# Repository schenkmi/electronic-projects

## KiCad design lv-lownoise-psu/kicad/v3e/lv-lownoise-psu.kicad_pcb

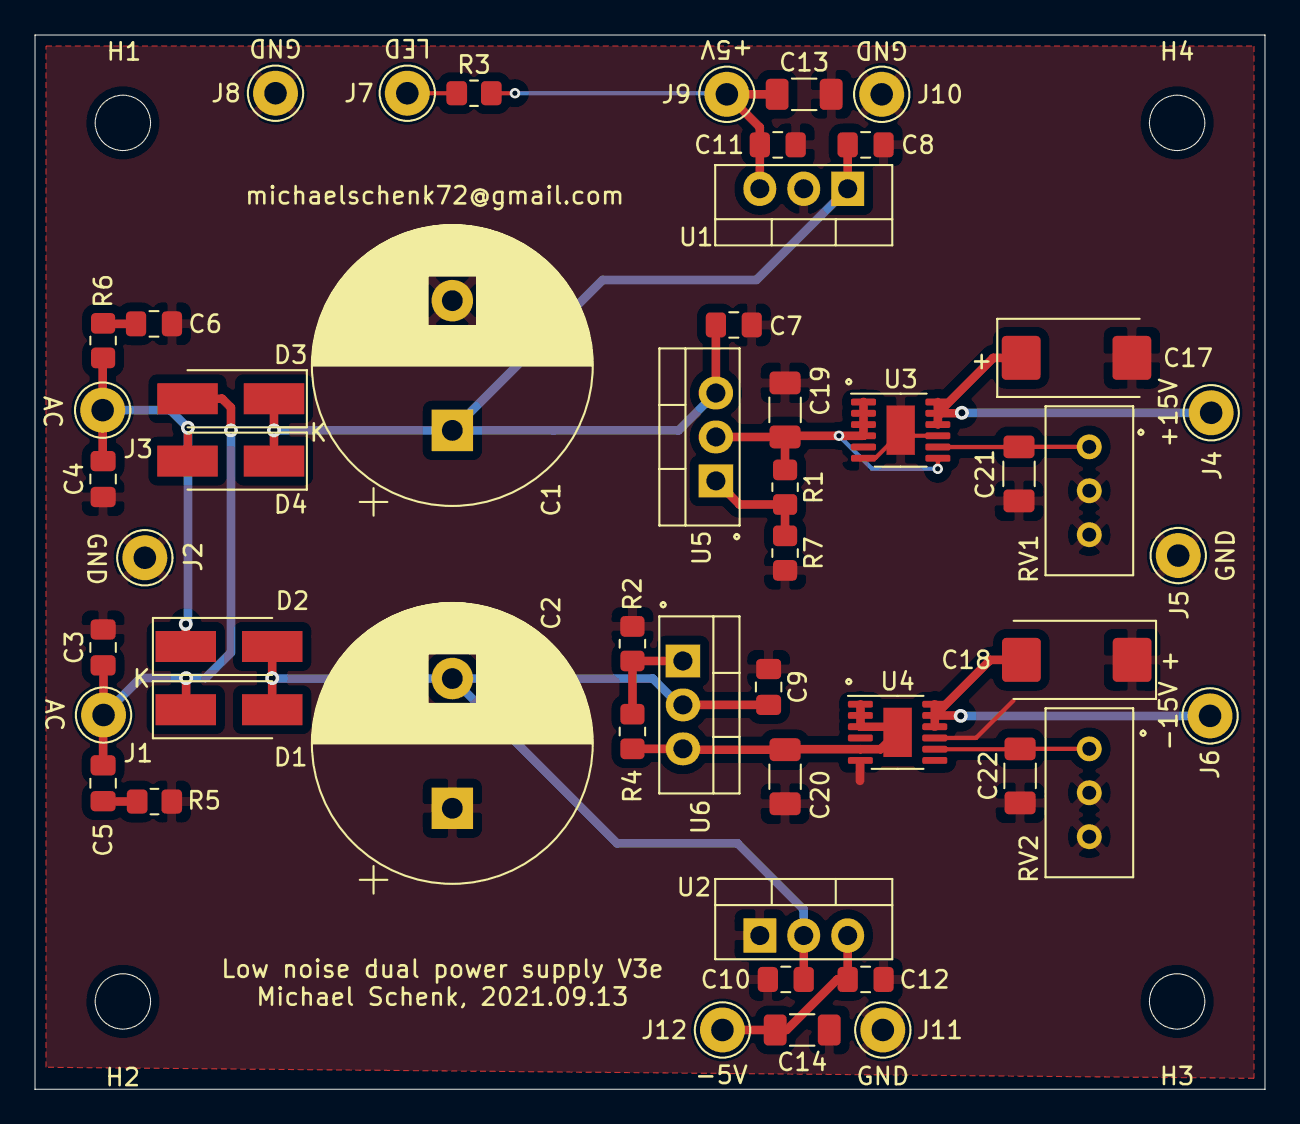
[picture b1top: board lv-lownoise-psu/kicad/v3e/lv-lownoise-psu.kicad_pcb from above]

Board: 2 copper layers, 71.1 x 61.0 mm, 55 parts (0 on the bottom side), 18 nets.

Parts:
C1, C2: 2200uF; CP_Radial_D16.0mm_P7.50mm
C3, C4: Cx/10nF/50V; C_0805_2012Metric_Pad1.18x1.45mm_HandSolder
C5, C6: Cs/50V; C_0805_2012Metric_Pad1.18x1.45mm_HandSolder
C7, C8, C9, C10: 330nF; C_0805_2012Metric_Pad1.18x1.45mm_HandSolder
C11, C12: 100nF; C_0805_2012Metric_Pad1.18x1.45mm_HandSolder
C13, C14: 10uF/25V; C_1206_3216Metric_Pad1.33x1.80mm_HandSolder
C17, C18: 33uF; CP_EIA-7343-31_Kemet-D_Pad2.25x2.55mm_HandSolder
C19, C20, C21, C22: 4.7uF/25V; C_1206_3216Metric_Pad1.33x1.80mm_HandSolder
D1, D2, D3, D4: BYG20D; D_SMA_Handsoldering
H1, H2, H3, H4: MountingHole; MountingHole_3.2mm_M3
J1, J3: AC; Pin_D1.3mm_L11.0mm
J2, J5, J8, J10, J11: GND; Pin_D1.3mm_L11.0mm
J4: +15V; Pin_D1.3mm_L11.0mm
J6: -15V; Pin_D1.3mm_L11.0mm
J7: LED; Pin_D1.3mm_L11.0mm
J9: +5V; Pin_D1.3mm_L11.0mm
J12: -5V; Pin_D1.3mm_L11.0mm
R1, R4: 270R; R_0805_2012Metric_Pad1.20x1.40mm_HandSolder
R2, R7: 3k3; R_0805_2012Metric_Pad1.20x1.40mm_HandSolder
R3: 240R; R_0805_2012Metric_Pad1.20x1.40mm_HandSolder
R5, R6: Rs/1/8W; R_0805_2012Metric_Pad1.20x1.40mm_HandSolder
RV1, RV2: 200k; Potentiometer_Bourns_3296W_Vertical
U1: LM7805_TO220; TO-220-3_Vertical
U2: LM7905_TO220; TO-220-3_Vertical
U3: LT3045xMSE; MSOP-12-1EP_3x4mm_P0.65mm_EP1.65x2.85mm
U4: LT3094xMSE; MSOP-12-1EP_3x4mm_P0.65mm_EP1.65x2.85mm
U5: LM317_TO-220; TO-220-3_Vertical
U6: LM337_TO220; TO-220-3_Vertical

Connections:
GND: C1.2, C2.1, C3.2, C4.1, C6.1, C7.2, C8.2, C9.1, C10.1, C11.2, C12.1, C13.2, C14.1, C17.2, C18.1, C19.2, C20.1, C21.2, C22.1, J2.1, J5.1, J8.1, J10.1, J11.1, R2.1, R5.2, R7.2, RV1.2, RV1.3, RV2.2, RV2.3, U1.2, U2.1, U3.6, U3.9, U3.13, U4.6, U4.9
unnamed: C1.1, C7.1, C8.1, D3.1, D4.1, U1.1, U5.3
unnamed: C3.1, C5.1, D1.1, D3.2, J1.1
unnamed: C4.2, D2.1, D4.2, J3.1, R6.2
unnamed: C5.2, R5.1
unnamed: C6.2, R6.1
unnamed: C2.2, C9.2, C10.2, D1.2, D2.2, U2.2, U6.2
unnamed: C11.1, C13.1, J9.1, R3.2, U1.3
unnamed: C12.2, C14.2, J12.1, U2.3
unnamed: C17.1, J4.1, U3.10, U3.11, U3.12
unnamed: C18.2, J6.1, U4.10, U4.11, U4.12
unnamed: C19.1, R1.1, U3.1, U3.2, U3.3, U3.4, U3.7, U5.2
unnamed: C20.2, R4.2, U4.1, U4.2, U4.3, U4.5, U4.13, U6.3
unnamed: C21.1, RV1.1, U3.8
unnamed: C22.2, RV2.1, U4.8
unnamed: J7.1, R3.1
unnamed: R1.2, R7.1, U5.1
unnamed: R2.2, R4.1, U6.1

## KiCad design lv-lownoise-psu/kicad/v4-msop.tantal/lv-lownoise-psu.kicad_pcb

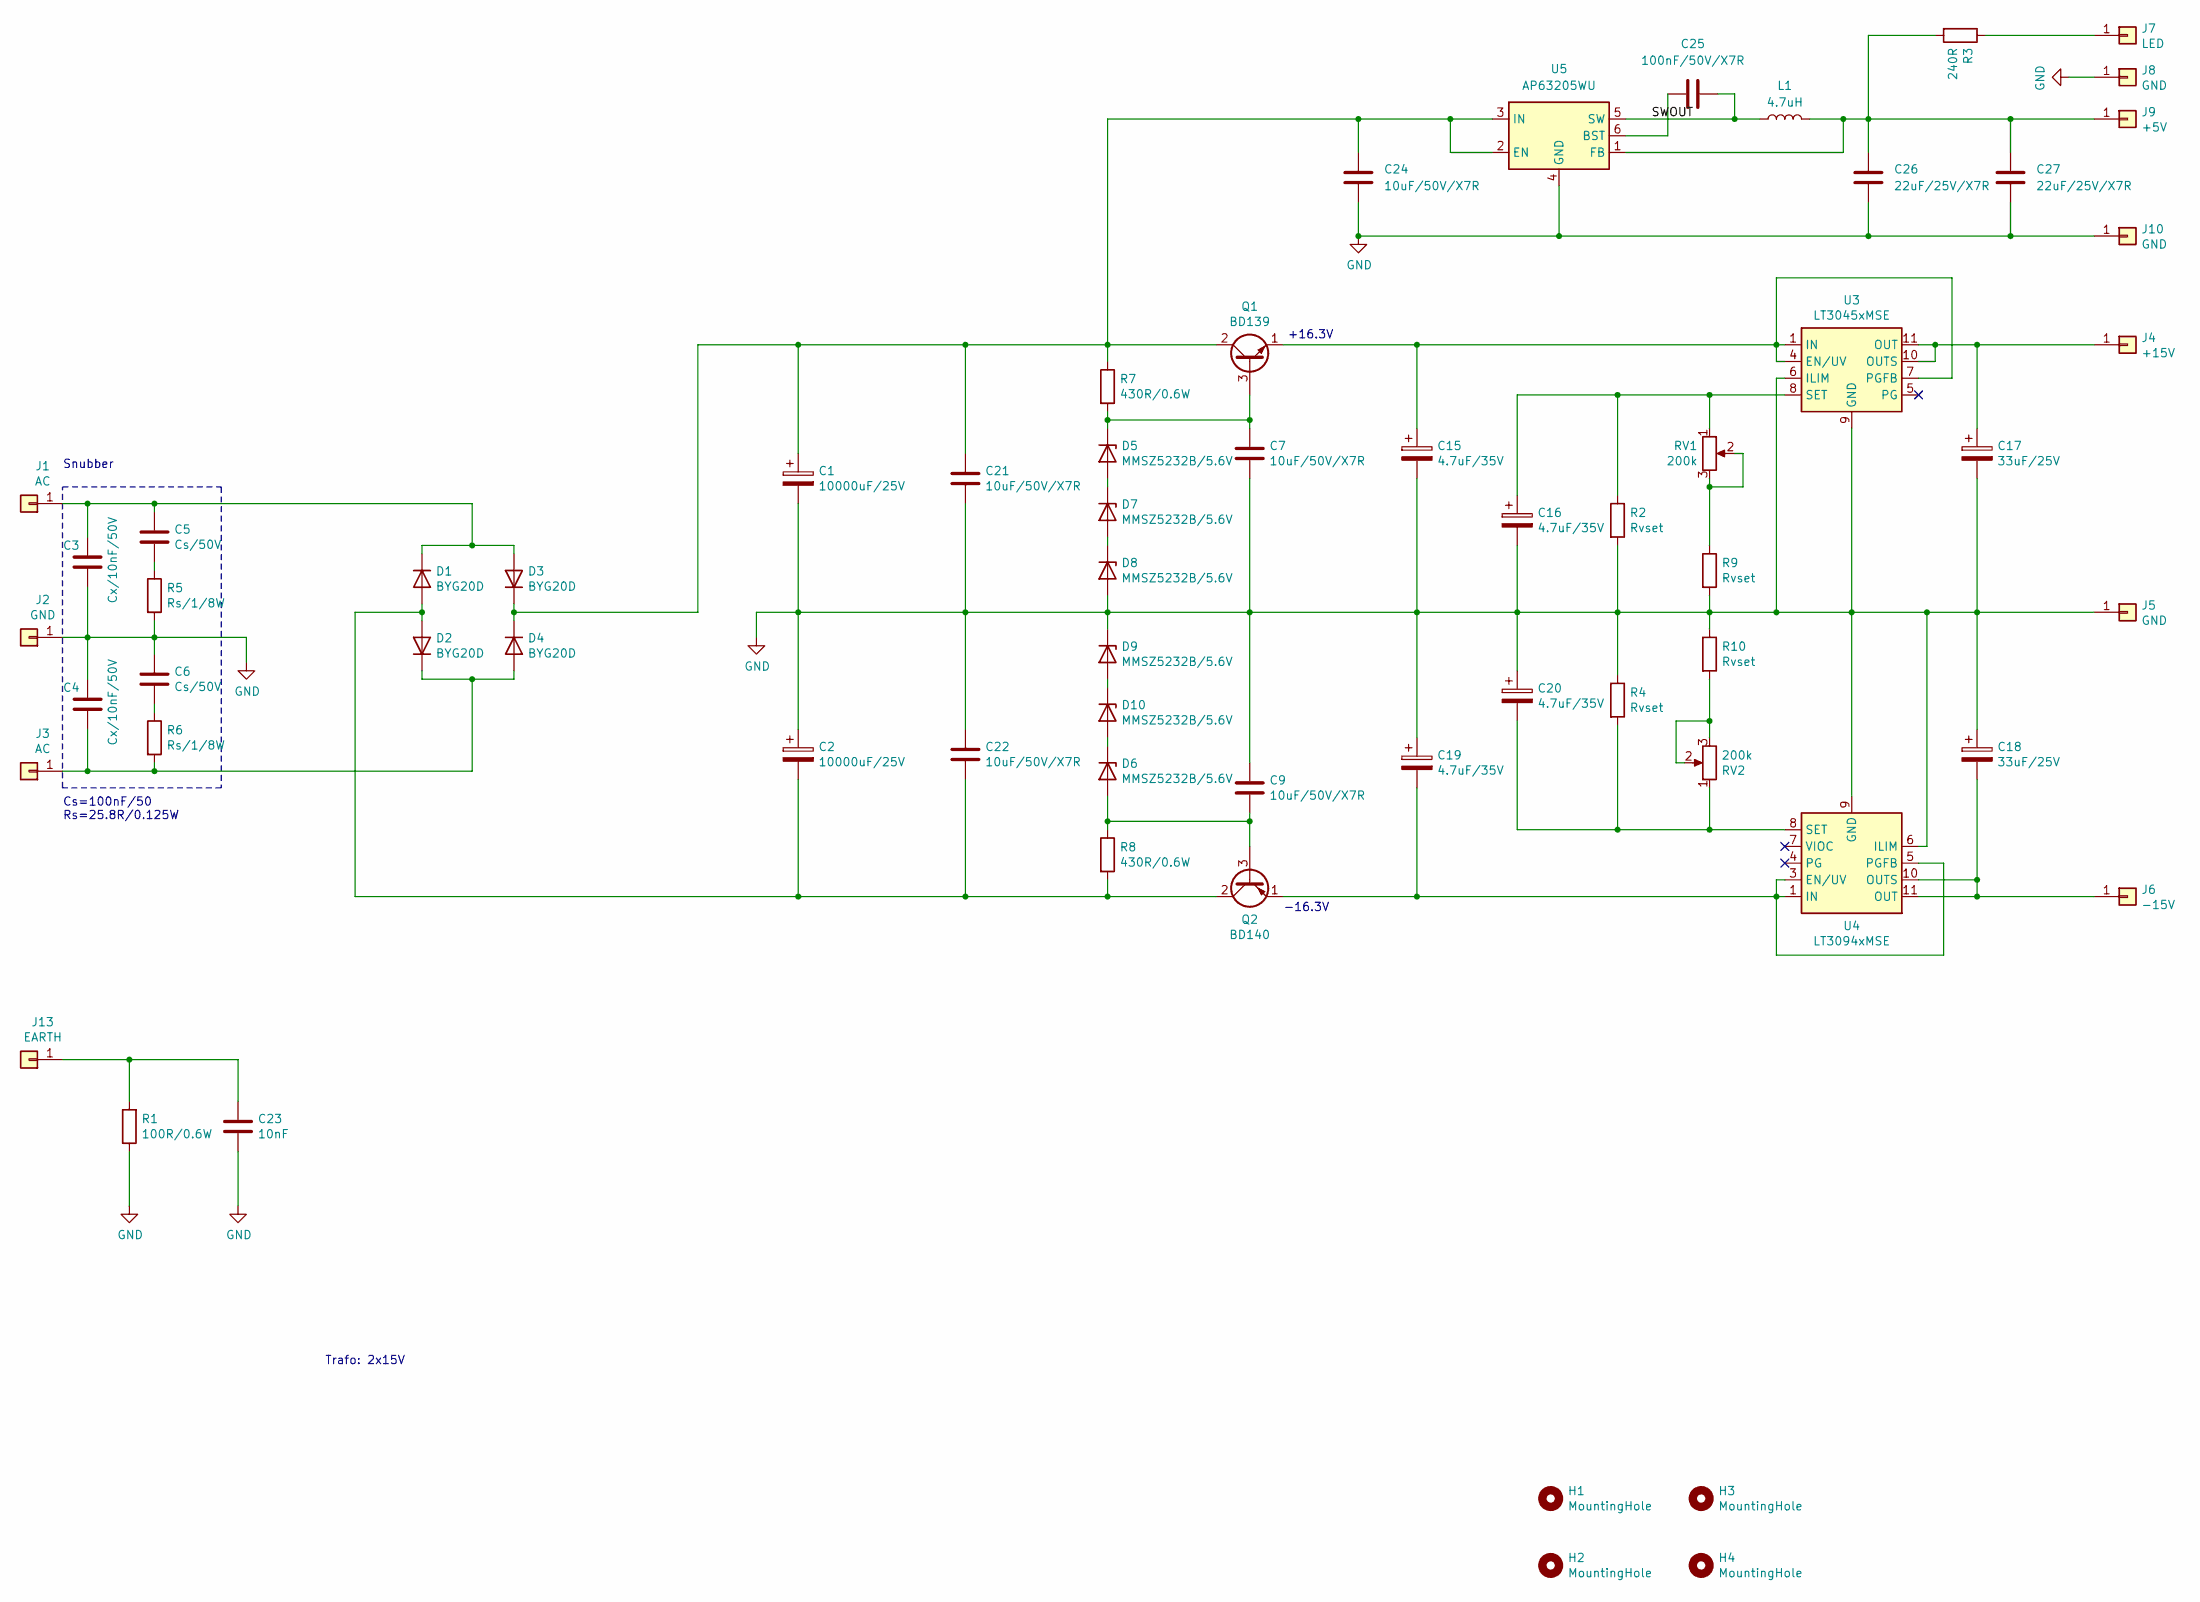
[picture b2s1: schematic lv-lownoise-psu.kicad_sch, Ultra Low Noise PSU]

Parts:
C1, C2: 10000uF/25V; CP_Radial_D25.0mm_P10.00mm_SnapIn
C3, C4: Cx/10nF/50V; C_0805_2012Metric_Pad1.18x1.45mm_HandSolder
C5, C6: Cs/50V; C_0805_2012Metric_Pad1.18x1.45mm_HandSolder
C7, C9, C21, C22, C24: 10uF/50V/X7R; C_1206_3216Metric_Pad1.33x1.80mm_HandSolder
C15, C16, C19, C20: 4.7uF/35V; CP_EIA-3528-15_AVX-H_Pad1.50x2.35mm_HandSolder
C17, C18: 33uF/25V; CP_EIA-7343-31_Kemet-D_Pad2.25x2.55mm_HandSolder
C23: 10nF; C_Rect_L7.2mm_W2.5mm_P5.00mm_FKS2_FKP2_MKS2_MKP2
C25: 100nF/50V/X7R; C_0603_1608Metric_Pad1.08x0.95mm_HandSolder
C26, C27: 22uF/25V/X7R; C_1210_3225Metric_Pad1.33x2.70mm_HandSolder
D1, D2, D3, D4: BYG20D; D_SMA_Handsoldering
D5, D6, D7, D8, D9, D10: MMSZ5232B/5.6V; D_SOD-123
H1, H2, H3, H4: MountingHole; MountingHole_3.2mm_M3
J1, J3: AC; Pin_D1.3mm_L11.0mm
J2: GND; Pin_D1.3mm_L11.0mm
J4: +15V; Pin_D1.0mm_L10.0mm
J5, J8, J10: GND; Pin_D1.0mm_L10.0mm
J6: -15V; Pin_D1.0mm_L10.0mm
J7: LED; Pin_D1.0mm_L10.0mm
J9: +5V; Pin_D1.0mm_L10.0mm
J13: EARTH; Pin_D1.3mm_L11.0mm
L1: 4.7uH; L_Bourns-SRN6028
Q1: BD139; TO-126-3_Vertical
Q2: BD140; TO-126-3_Vertical
R1: 100R/0.6W; R_Axial_DIN0207_L6.3mm_D2.5mm_P10.16mm_Horizontal
R2, R4, R9, R10: Rvset; R_0805_2012Metric_Pad1.20x1.40mm_HandSolder
R3: 240R; R_0805_2012Metric_Pad1.20x1.40mm_HandSolder
R5, R6: Rs/1/8W; R_0805_2012Metric_Pad1.20x1.40mm_HandSolder
R7, R8: 430R/0.6W; R_Axial_DIN0207_L6.3mm_D2.5mm_P10.16mm_Horizontal
RV1, RV2: 200k; Potentiometer_Bourns_3296W_Vertical
U3: LT3045xMSE; MSOP-12-1EP_3x4mm_P0.65mm_EP1.65x2.85mm
U4: LT3094xMSE; MSOP-12-1EP_3x4mm_P0.65mm_EP1.65x2.85mm
U5: AP63205WU; TSOT-23-6

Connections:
/SWOUT: C25.1, L1.1, U5.5 (SW)
GND: C1.2, C2.1, C3.2, C4.1, C6.1, C7.2, C9.1, C15.2, C16.2, C17.2, C18.1, C19.1, C20.1, C21.2, C22.1, C23.2, C24.2, C26.2, C27.2, D8.2 (A), D9.1 (K), J2.1, J5.1, J8.1, J10.1, R1.1, R2.2, R4.1, R5.2, R9.2, R10.1, U3.6 (ILIM), U3.9 (GND), U3.13 (GND), U4.6 (ILIM), U4.9 (GND), U5.4 (GND)
unnamed: C5.2, R5.1
unnamed: C6.2, R6.1
unnamed: C2.2, C22.2, D1.2 (A), D2.2 (A), Q2.2 (C), R8.2
unnamed: C3.1, C5.1, D1.1 (K), D3.2 (A), J1.1
unnamed: C4.2, D2.1 (K), D4.2 (A), J3.1, R6.2
unnamed: C1.1, C21.1, C24.1, D3.1 (K), D4.1 (K), Q1.2 (C), R7.1, U5.2 (EN), U5.3 (IN)
unnamed: D5.2 (A), D7.1 (K)
unnamed: C7.1, D5.1 (K), Q1.3 (B), R7.2
unnamed: C9.2, D6.2 (A), Q2.3 (B), R8.1
unnamed: D7.2 (A), D8.1 (K)
unnamed: D6.1 (K), D10.2 (A)
unnamed: D9.2 (A), D10.1 (K)
unnamed: C17.1, J4.1, U3.10 (OUTS), U3.11 (OUT), U3.12 (OUT)
unnamed: C18.2, J6.1, U4.10 (OUTS), U4.11 (OUT), U4.12 (OUT)
unnamed: J7.1, R3.1
unnamed: C26.1, C27.1, J9.1, L1.2, R3.2, U5.1 (FB)
unnamed: C23.1, J13.1, R1.2
unnamed: C15.1, Q1.1 (E), U3.1 (IN), U3.2 (IN), U3.3 (IN), U3.4 (EN/UV), U3.7 (PGFB)
unnamed: C19.2, Q2.1 (E), U4.1 (IN), U4.2 (IN), U4.3 (EN/UV), U4.5 (PGFB), U4.13 (IN)
unnamed: R9.1, RV1.2, RV1.3
unnamed: R10.2, RV2.2, RV2.3
unnamed: C16.1, R2.1, RV1.1, U3.8 (SET)
unnamed: C20.2, R4.2, RV2.1, U4.8 (SET)
unnamed: C25.2, U5.6 (BST)

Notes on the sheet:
+16.3V
Snubber
Trafo: 2x15V
Cs=100nF/50 Rs=25.8R/0.125W
-16.3V

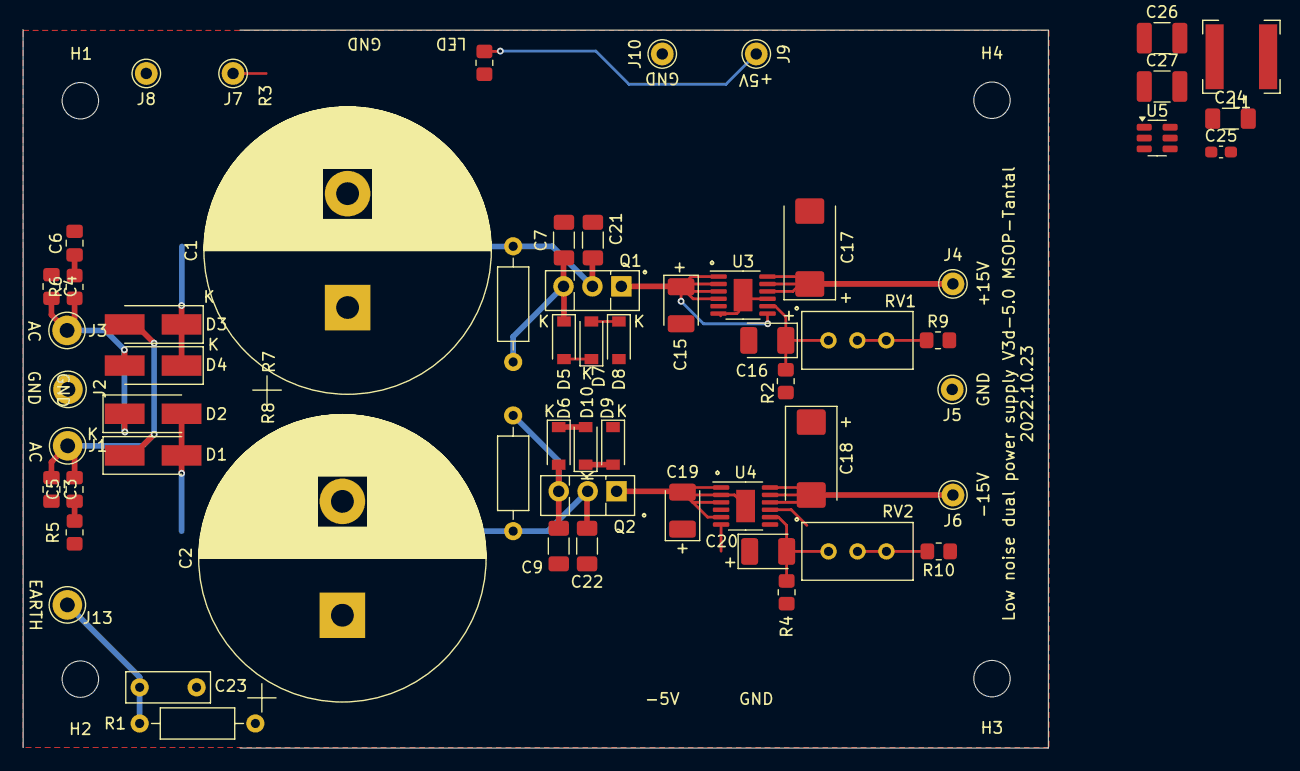
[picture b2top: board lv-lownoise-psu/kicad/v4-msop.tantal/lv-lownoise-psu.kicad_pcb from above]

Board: 2 copper layers, 90.0 x 63.1 mm, 64 parts (0 on the bottom side), 26 nets.
